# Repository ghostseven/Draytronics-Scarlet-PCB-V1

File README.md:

# Draytronics-Scarlet-PCB-V1

A open source 17 key numpad keyboard, designed to be easily built at home with through hole components. More info / kits / PCB designs available at https://www.draytronics.co.uk/scarlet

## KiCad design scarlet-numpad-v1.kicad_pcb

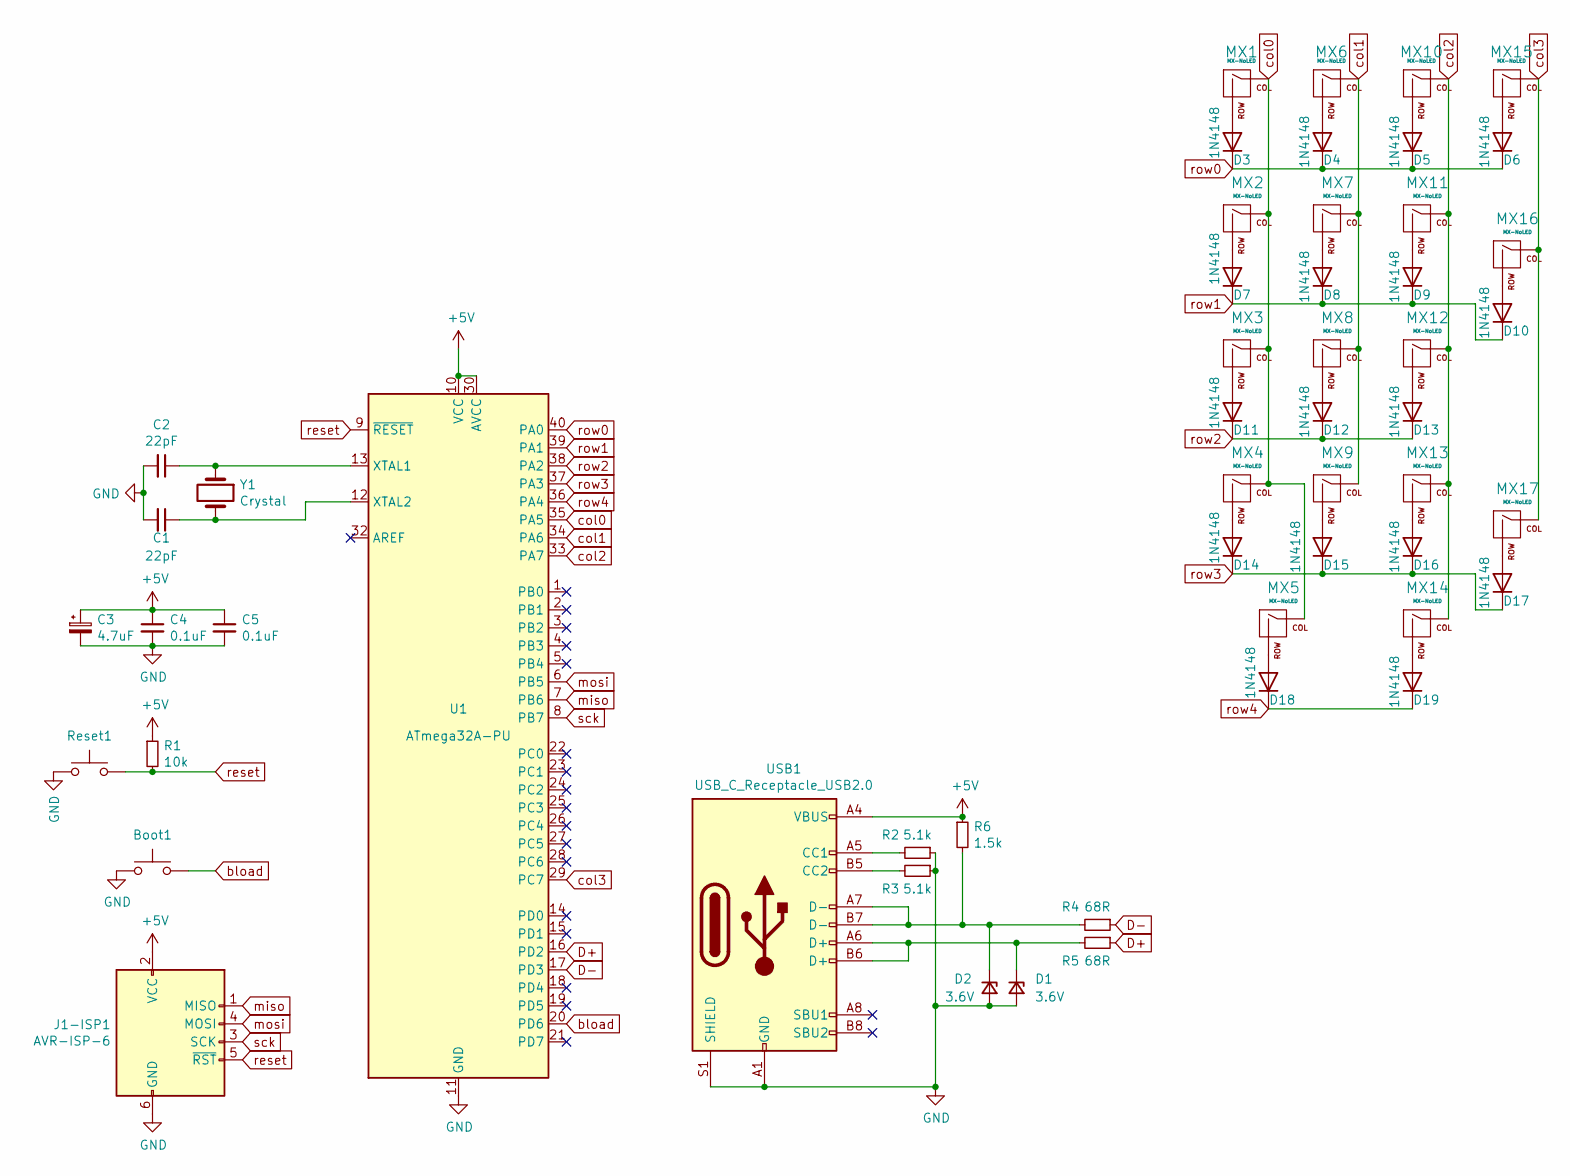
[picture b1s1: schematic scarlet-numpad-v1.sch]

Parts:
Boot1: Bootloader; SW_PUSH_6mm
C1, C2: 22pF; C_Disc_D3.0mm_W1.6mm_P2.50mm
C3: 4.7uF; CP_Radial_D4.0mm_P1.50mm
C4, C5: 0.1uF; C_Disc_D4.3mm_W1.9mm_P5.00mm
D1, D2: 3.6V; D_DO-35_SOD27_P5.08mm_Horizontal
D3, D4, D5, D6, D7, D8, D9, D10, D11, D12, D13, D14, D15, D16, D17, D18, D19: 1N4148; D_DO-35_SOD27_P5.08mm_Horizontal
J1-ISP1: AVR-ISP-6; IDC-Header_2x03_P2.54mm_Vertical
MX1, MX2, MX3, MX4, MX6, MX7, MX8, MX9, MX10, MX11, MX12, MX13, MX14, MX15: MX-NoLED; SW_Cherry_MX_1.00u_PCB
MX5: MX-NoLED; SW_Cherry_MX_2.00u_PCB
MX16, MX17: MX-NoLED; SW_Cherry_MX_2.00u_Vertical_PCB
R1: 10k; R_Axial_DIN0204_L3.6mm_D1.6mm_P7.62mm_Horizontal
R2, R3: 5.1k; R_Axial_DIN0204_L3.6mm_D1.6mm_P7.62mm_Horizontal
R4, R5: 68R; R_Axial_DIN0204_L3.6mm_D1.6mm_P7.62mm_Horizontal
R6: 1.5k; R_Axial_DIN0204_L3.6mm_D1.6mm_P7.62mm_Horizontal
Reset1: Reset; SW_PUSH_6mm
U1: ATmega32A-PU; DIP-40_W15.24mm
USB1: USB_C_Receptacle_USB2.0; USB_C_GCT_USB4085
Y1: Crystal; Crystal_HC49-U_Vertical

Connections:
+5V: C3.1, C4.1, C5.1, J1-ISP1.2 (VCC), R1.1, R6.1, U1.10 (VCC), U1.30 (AVCC), USB1.A4 (VBUS), USB1.A9 (VBUS), USB1.B4 (VBUS), USB1.B9 (VBUS)
D+: R5.1, U1.16 (PD2)
D-: R4.1, U1.17 (PD3)
GND: Boot1.1, C1.2, C2.2, C3.2, C4.2, C5.2, D1.2 (A), D2.2 (A), J1-ISP1.6 (GND), R2.1, R3.1, Reset1.1, U1.11 (GND), U1.31 (GND), USB1.A1 (GND), USB1.A12 (GND), USB1.B1 (GND), USB1.B12 (GND), USB1.S1 (SHIELD); also elsewhere on the board
unnamed: C1.1, U1.12 (XTAL2), Y1.2
unnamed: C2.1, U1.13 (XTAL1), Y1.1
unnamed: D1.1 (K), R5.2, USB1.A6 (D+), USB1.B6 (D+)
unnamed: D2.1 (K), R4.2, R6.2, USB1.A7 (D-), USB1.B7 (D-)
unnamed: D3.2 (A), MX1.2 (ROW)
unnamed: D4.2 (A), MX6.2 (ROW)
unnamed: D5.2 (A), MX10.2 (ROW)
unnamed: D6.2 (A), MX15.2 (ROW)
unnamed: D7.2 (A), MX2.2 (ROW)
unnamed: D8.2 (A), MX7.2 (ROW)
unnamed: D9.2 (A), MX11.2 (ROW)
unnamed: D10.2 (A), MX16.2 (ROW)
unnamed: D11.2 (A), MX3.2 (ROW)
unnamed: D12.2 (A), MX8.2 (ROW)
unnamed: D13.2 (A), MX12.2 (ROW)
unnamed: D14.2 (A), MX4.2 (ROW)
unnamed: D15.2 (A), MX9.2 (ROW)
unnamed: D16.2 (A), MX13.2 (ROW)
unnamed: D17.2 (A), MX17.2 (ROW)
unnamed: D18.2 (A), MX5.2 (ROW)
unnamed: D19.2 (A), MX14.2 (ROW)
unnamed: R2.2, USB1.A5 (CC1)
unnamed: R3.2, USB1.B5 (CC2)
bload: Boot1.2, U1.20 (PD6); also elsewhere on the board
col0: MX1.1 (COL), MX2.1 (COL), MX3.1 (COL), MX4.1 (COL), MX5.1 (COL), U1.35 (PA5)
col1: MX6.1 (COL), MX7.1 (COL), MX8.1 (COL), MX9.1 (COL), U1.34 (PA6)
col2: MX10.1 (COL), MX11.1 (COL), MX12.1 (COL), MX13.1 (COL), MX14.1 (COL), U1.33 (PA7)
col3: MX15.1 (COL), MX16.1 (COL), MX17.1 (COL), U1.29 (PC7)
miso: J1-ISP1.1 (MISO), U1.7 (PB6)
mosi: J1-ISP1.4 (MOSI), U1.6 (PB5)
reset: J1-ISP1.5 (~RST), R1.2, Reset1.2, U1.9 (~RESET); also elsewhere on the board
row0: D3.1 (K), D4.1 (K), D5.1 (K), D6.1 (K), U1.40 (PA0)
row1: D7.1 (K), D8.1 (K), D9.1 (K), D10.1 (K), U1.39 (PA1)
row2: D11.1 (K), D12.1 (K), D13.1 (K), U1.38 (PA2)
row3: D14.1 (K), D15.1 (K), D16.1 (K), D17.1 (K), U1.37 (PA3)
row4: D18.1 (K), D19.1 (K), U1.36 (PA4)
sck: J1-ISP1.3 (SCK), U1.8 (PB7)

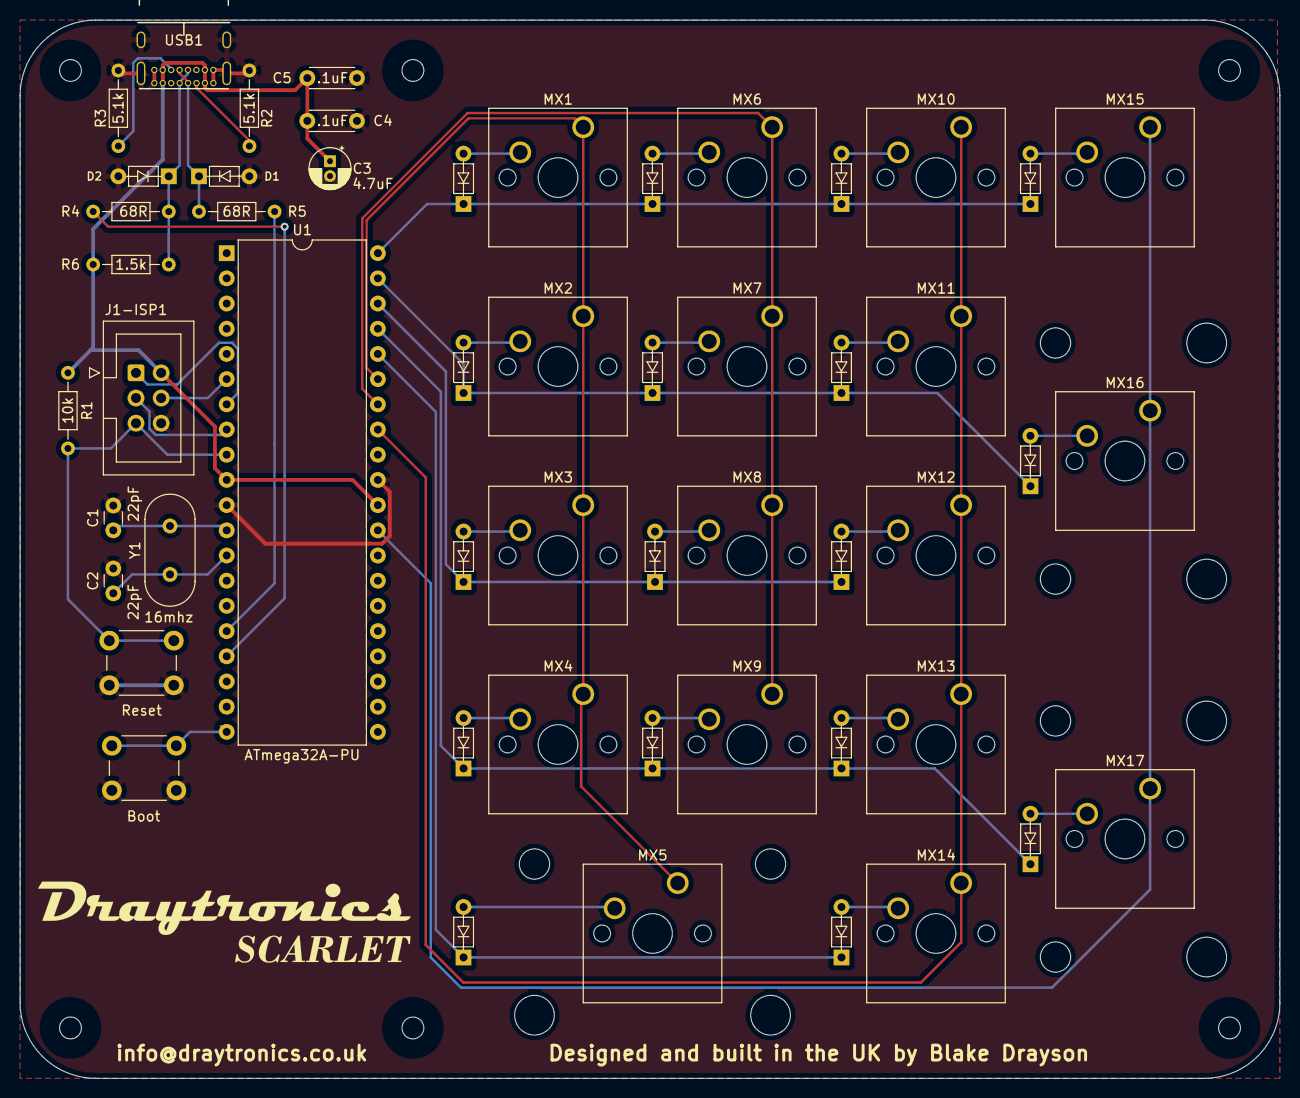
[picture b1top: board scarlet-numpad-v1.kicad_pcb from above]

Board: 2 copper layers, 127.0 x 106.7 mm, 53 parts (0 on the bottom side), 41 nets.

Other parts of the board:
Boot: Bootloader; SW_PUSH_6mm
Reset: Reset; SW_PUSH_6mm

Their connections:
GND: Boot.1, Reset.1; also elsewhere on the board
bload: Boot.2; also elsewhere on the board
reset: Reset.2; also elsewhere on the board

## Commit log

2020-11-15 Added laser cutting files for acrylic case
2020-12-29 Added PCB renders
2020-12-30 Readme update.
